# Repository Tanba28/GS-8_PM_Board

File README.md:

# GS-8_PM_Board
GS-8 Power Management Board

Master project -> [project-arrows/GS-8](https://github.com/project-arrows/GS-8)

## Overview
 * GS-8電源管理基板

## Role
 * 外部電源と内部電源の切り替えを行う。
 * 内部電源の電流・電圧を監視する。
 * 内部電源の電圧が規定値を下回った際にカットオフを行う。
 * CANバスを監視しロギングする。

## Link
 * [Tanba28/GS-8_PD_Board](https://github.com/Tanba28/GS-8_PD_Board)
 * [Tanba28/GS-8_Barometer](https://github.com/Tanba28/GS-8_Barometer)
 * [Tanba28/GS-8_Motion_Logger](https://github.com/Tanba28/GS-8_Motion_Logger)
 * [Tanba28/GS-8_Relay_Board](https://github.com/Tanba28/GS-8_Relay_Board)
 * [ringo156/GS-8_ACCLRM_Board](https://github.com/ringo156/GS-8_ACCLRM_Board)
 * [takamasavvv/RCT-X_Logger](https://github.com/takamasavvv/RCT-X-Logger)
 * [takamasavvv/RCT-X-Telemetry](https://github.com/takamasavvv/RCT-X-Telemetry)
 
## LICENSE
MIT License

Copyright (c) 2019 Tanba28

Permission is hereby granted, free of charge, to any person obtaining a copy
of this software and associated documentation files (the "Software"), to deal
in the Software without restriction, including without limitation the rights
to use, copy, modify, merge, publish, distribute, sublicense, and/or sell
copies of the Software, and to permit persons to whom the Software is
furnished to do so, subject to the following conditions:

The above copyright notice and this permission notice shall be included in all
copies or substantial portions of the Software.

THE SOFTWARE IS PROVIDED "AS IS", WITHOUT WARRANTY OF ANY KIND, EXPRESS OR
IMPLIED, INCLUDING BUT NOT LIMITED TO THE WARRANTIES OF MERCHANTABILITY,
FITNESS FOR A PARTICULAR PURPOSE AND NONINFRINGEMENT. IN NO EVENT SHALL THE
AUTHORS OR COPYRIGHT HOLDERS BE LIABLE FOR ANY CLAIM, DAMAGES OR OTHER
LIABILITY, WHETHER IN AN ACTION OF CONTRACT, TORT OR OTHERWISE, ARISING FROM,
OUT OF OR IN CONNECTION WITH THE SOFTWARE OR THE USE OR OTHER DEALINGS IN THE
SOFTWARE.

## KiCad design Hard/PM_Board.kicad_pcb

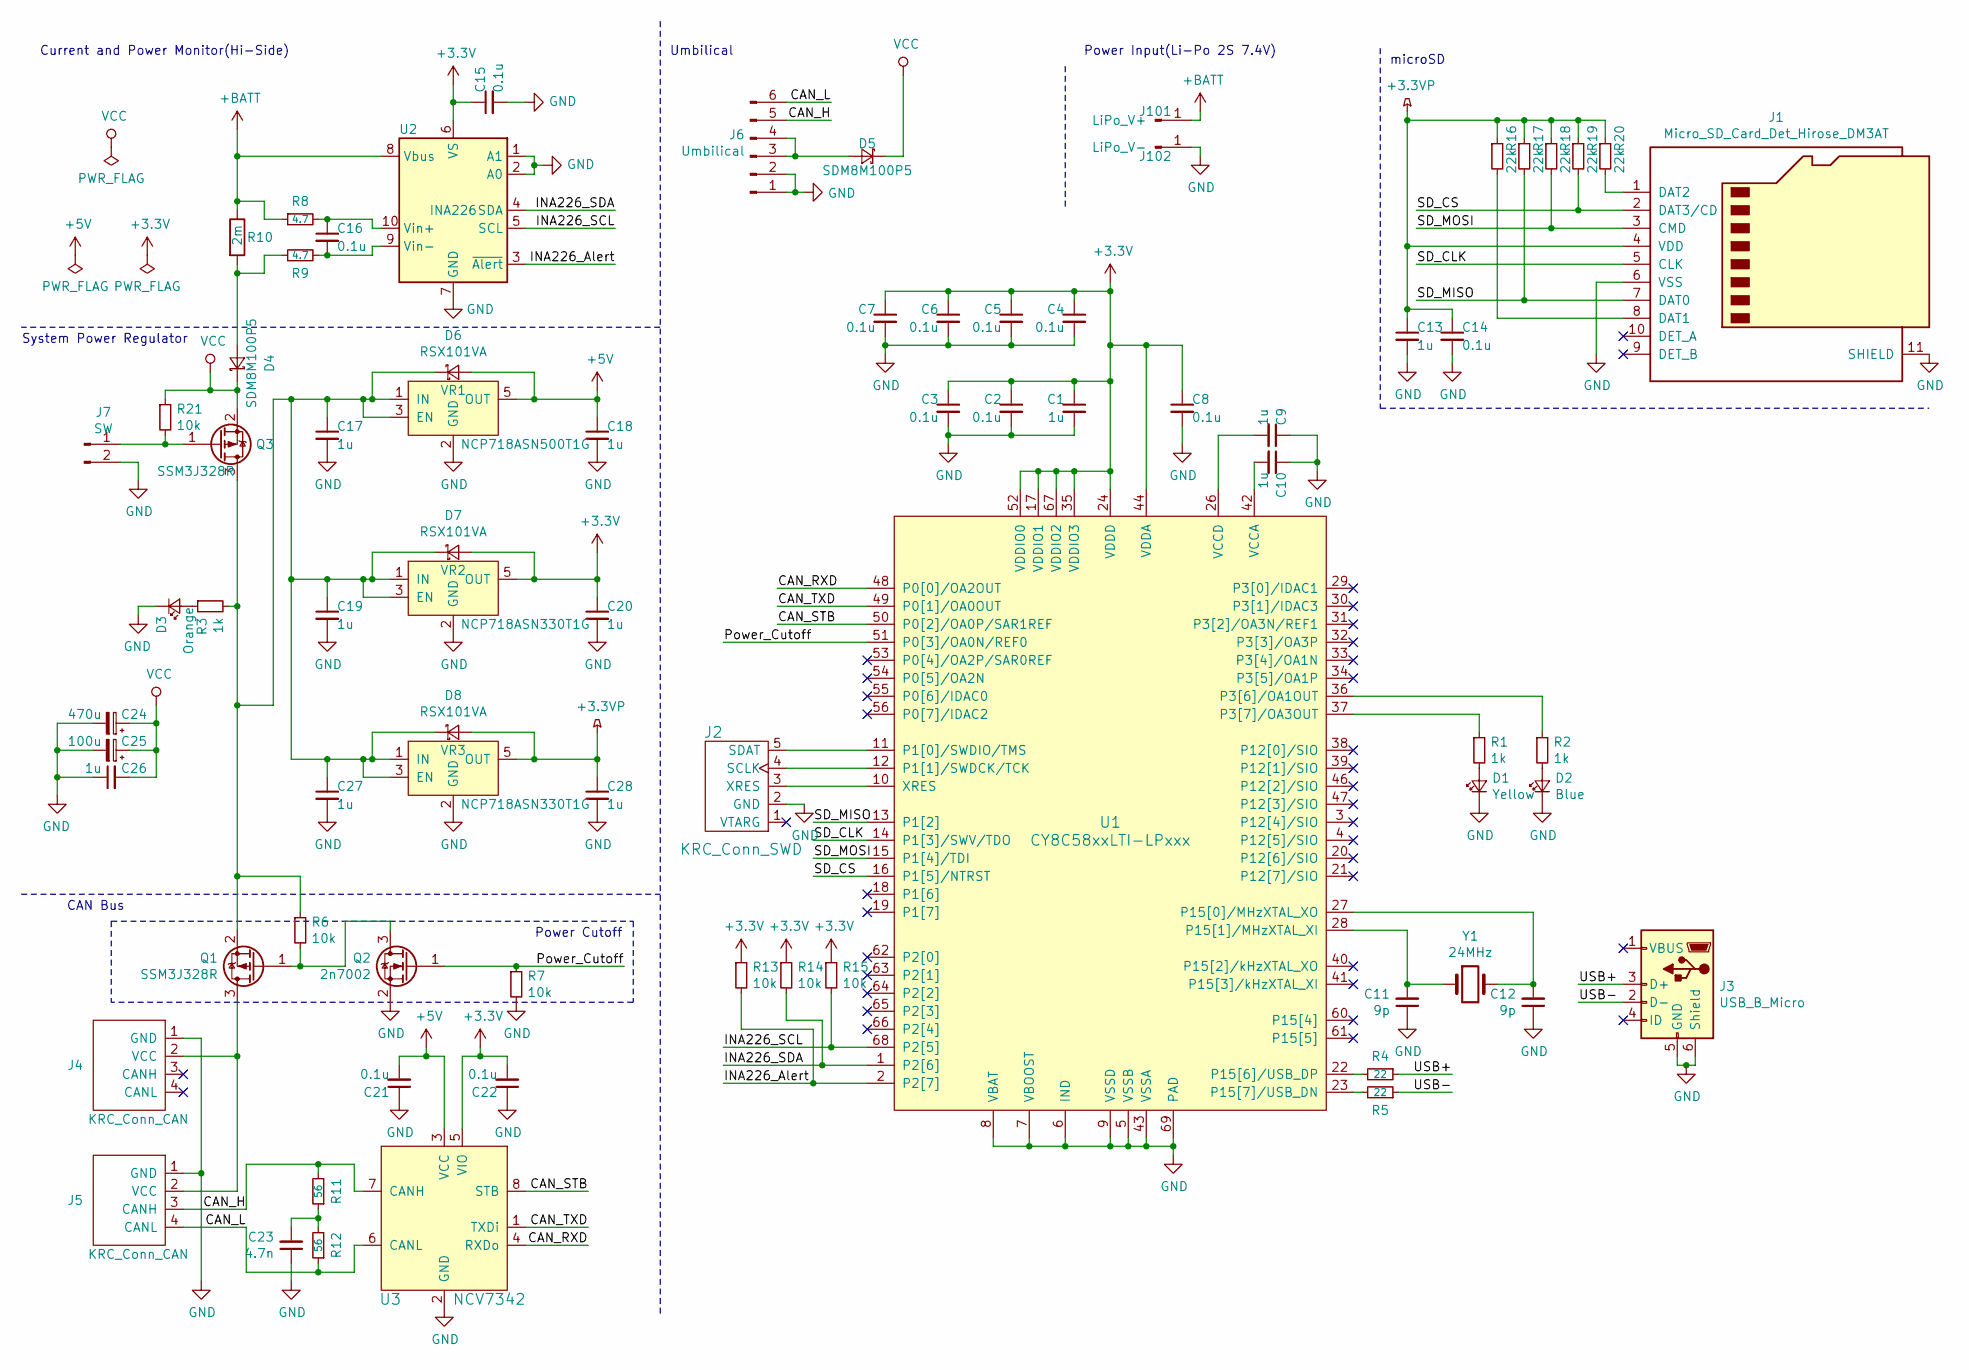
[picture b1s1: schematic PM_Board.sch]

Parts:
C1, C9, C10, C13, C17, C18, C19, C20, C26, C27, C28: 1u; C_0402_1005Metric; MPN GRM155R61E105KA12D
C2, C3, C4, C5, C6, C7, C8, C14, C15, C16, C21, C22: 0.1u; C_0402_1005Metric; MPN GRM155R62A104KE14D
C11, C12: 9p; C_0402_1005Metric; MPN GRM1555C1H9R0DA01D
C23: 4.7n; C_0402_1005Metric; MPN GRM155R71H472KA01D
C24: 470u; CP_Elec_10x10; MPN UWT1E471MNL1GS
C25: 100u; CP_Elec_6.3x7.7; MPN UWT1E101MCL1GS
D1: Yellow; LED_0603_1608Metric
D2: Blue; LED_0603_1608Metric
D3: Orange; LED_0603_1608Metric
D4, D5: SDM8M100P5; D_PowerDI5; MPN SDM8M100P5-13
D6, D7, D8: RSX101VA; D_TUMD2; MPN RSX101VAM-30TR
J1: Micro_SD_Card_Det_Hirose_DM3AT; microSD_HC_Hirose_DM3AT-SF-PEJM5; MPN DM3AT-SF-PEJM5
J2: KRC_Conn_SWD; JST_JQ_05JQ-BT_1x05_P2.5mm_Vertical; MPN 05JQ-BT
J3: USB_B_Micro; Hirose_ZX_ZX62D-B-5P8; MPN ZX62D-B-5P8(30)
J4, J5: KRC_Conn_CAN; JST_XH_S4B-XH-A_1x04_P2.50mm_Horizontal; MPN S4B-XH-A
J6: Umbilical; Hirose_DF1E_DF1E-6P-2.5DS_1x06_P2.5mm_Vertical; MPN DF1EC-6P-2.5DSA(35)
J7: SW; Hirose_DF1E_DF1E-2P-2.5DS_1x02_P2.5mm_Vertical; MPN DF1EC-2P-2.5DSA(35)
J101: LiPo_V+; MountingHole_2.2mm_M2_Pad_Via
J102: LiPo_V-; MountingHole_2.2mm_M2_Pad_Via
Q1, Q3: SSM3J328R; SOT-23; MPN SSM3J328R,LF
Q2: 2n7002; SOT-23; MPN 2N7002
R1, R2, R3: 1k; R_0402_1005Metric; MPN ERJ-2GEJ102X
R4, R5: 22; R_0402_1005Metric; MPN ERJ-2GEJ220X
R6, R7, R13, R14, R15, R21: 10k; R_0402_1005Metric; MPN ERJ-2GEJ103X
R8, R9: 4.7; R_0402_1005Metric; MPN ERJ-2GEJ4R7X
R10: 2m; R_0805_2012Metric; MPN PMR10EZPFV2L00
R11, R12: 56; R_0402_1005Metric; MPN ERJ-2GEJ560X
R16, R17, R18, R19, R20: 22k; R_0402_1005Metric; MPN ERJ-2RKF2202X
U1: CY8C58xxLTI-LPxxx; Cypress_QFN-68_EP_8x8_Pitch0.4mm; MPN CY8C5868LTI-LP039
U2: INA226; MSOP-10_3x3mm_P0.5mm; MPN INA226AIDGSR
U3: NCV7342; DFN-8-1EP_3x3mm_P0.65mm_EP1.55x2.4mm; MPN NCV7342MW3R2G
VR1: NCP718ASN500T1G; TSOT-23-5; MPN NCP718ASN500T1G
VR2, VR3: NCP718ASN330T1G; TSOT-23-5; MPN NCP718ASN330T1G
Y1: 24MHz; Crystal_Murata_XRCHA; MPN XRCHA24M000F0A01R0

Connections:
+3.3VP: C13.1, C14.1, C28.1, D8.2 (A), J1.4 (VDD), R16.1, R17.1, R18.1, R19.1, R20.1, VR3.5 (OUT)
+3V3: C1.1, C2.1, C3.1, C4.1, C5.1, C6.1, C7.1, C8.1, C15.1, C20.1, C22.2, D7.2 (A), R13.1, R14.1, R15.1, U1.17 (VDDIO1), U1.24 (VDDD), U1.35 (VDDIO3), U1.44 (VDDA), U1.52 (VDDIO0), U1.59 (VDDD), U1.67 (VDDIO2), U2.6 (VS), U3.5 (VIO), VR2.5 (OUT)
+5V: C18.1, C21.2, D6.2 (A), U3.3 (VCC), VR1.5 (OUT)
+BATT: J101.1, R8.1, R10.1, U2.8 (Vbus)
/CAN_H: J5.3 (CANH), J6.5, R11.2, U3.7 (CANH)
/CAN_L: J5.4 (CANL), J6.6, R12.1, U3.6 (CANL)
/CAN_RXD: U1.48 (P0[0]/OA2OUT), U3.4 (RXDo)
/CAN_STB: U1.50 (P0[2]/OA0P/SAR1REF), U3.8 (STB)
/CAN_TXD: U1.49 (P0[1]/OA0OUT), U3.1 (TXDi)
/INA226_Alert: R13.2, U1.2 (P2[7]), U2.3 (~Alert~)
/INA226_SCL: R15.2, U1.68 (P2[5]), U2.5 (SCL)
/INA226_SDA: R14.2, U1.1 (P2[6]), U2.4 (SDA)
/Power_Cutoff: Q2.1 (G), R7.1, U1.51 (P0[3]/OA0N/REF0)
/SD_CLK: J1.5 (CLK), U1.14 (P1[3]/SWV/TDO)
/SD_CS: J1.2 (DAT3/CD), R19.2, U1.16 (P1[5]/NTRST)
/SD_MISO: J1.7 (DAT0), R17.2, U1.13 (P1[2])
/SD_MOSI: J1.3 (CMD), R18.2, U1.15 (P1[4]/TDI)
/USB+: J3.3 (D+), R4.1
/USB-: J3.2 (D-), R5.1
GND: C1.2, C2.2, C3.2, C4.2, C5.2, C6.2, C7.2, C8.2, C9.1, C10.1, C11.1, C12.1, C13.2, C14.2, C15.2, C17.2, C18.2, C19.2, C20.2, C21.1, C22.1, C23.1, C24.2, C25.2, C26.1, C27.2, C28.2, D1.1 (K), D2.1 (K), D3.1 (K), J1.6 (VSS), J1.11 (SHIELD), J2.2 (GND), J3.5 (GND), J3.6 (Shield), J4.1 (GND), J5.1 (GND), J6.1, J6.2, J7.2, J102.1, Q2.2 (S), R7.2, U1.5 (VSSB), U1.6 (IND), U1.7 (VBOOST), U1.8 (VBAT), U1.9 (VSSD), U1.25 (VSSD), U1.43 (VSSA), U1.45 (VSSD), U1.58 (VSSD), U1.69 (PAD), U2.1 (A1), U2.2 (A0), U2.7 (GND), U3.2 (GND), U3.9, VR1.2 (GND), VR2.2 (GND), VR3.2 (GND)
unnamed: C9.2, U1.26 (VCCD), U1.57 (VCCD)
unnamed: C10.2, U1.42 (VCCA)
unnamed: C11.2, U1.28 (P15[1]/MHzXTAL_XI), Y1.1
unnamed: C12.2, U1.27 (P15[0]/MHzXTAL_XO), Y1.2
unnamed: C16.1, R8.2, U2.10 (Vin+)
unnamed: C16.2, R9.2, U2.9 (Vin-)
unnamed: C17.1, C19.1, C27.1, D6.1 (K), D7.1 (K), D8.1 (K), Q1.2 (S), Q3.3 (D), R3.2, R6.1, VR1.1 (IN), VR1.3 (EN), VR2.1 (IN), VR2.3 (EN), VR3.1 (IN), VR3.3 (EN)
unnamed: C23.2, R11.1, R12.2
unnamed: D1.2 (A), R1.2
unnamed: D2.2 (A), R2.2
unnamed: D3.2 (A), R3.1
unnamed: D4.2 (A), R9.1, R10.2
unnamed: D5.2 (A), J6.3, J6.4
unnamed: J1.1 (DAT2), R20.2
unnamed: J1.8 (DAT1), R16.2
unnamed: J2.3 (XRES), U1.10 (XRES)
unnamed: J2.4 (SCLK), U1.12 (P1[1]/SWDCK/TCK)
unnamed: J2.5 (SDAT), U1.11 (P1[0]/SWDIO/TMS)
unnamed: J4.2 (VCC), J5.2 (VCC), Q1.3 (D)
unnamed: J7.1, Q3.1 (G), R21.2
unnamed: Q1.1 (G), Q2.3 (D), R6.2
unnamed: R1.1, U1.37 (P3[7]/OA3OUT)
unnamed: R2.1, U1.36 (P3[6]/OA1OUT)
unnamed: R4.2, U1.22 (P15[6]/USB_DP)
unnamed: R5.2, U1.23 (P15[7]/USB_DN)
VCC: C24.1, C25.1, C26.2, D4.1 (K), D5.1 (K), Q3.2 (S), R21.1

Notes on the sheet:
Power Input(Li-Po 2S 7.4V)
Current and Power Monitor(Hi-Side)
System Power Regulator
CAN Bus
Power Cutoff
Umbilical
microSD

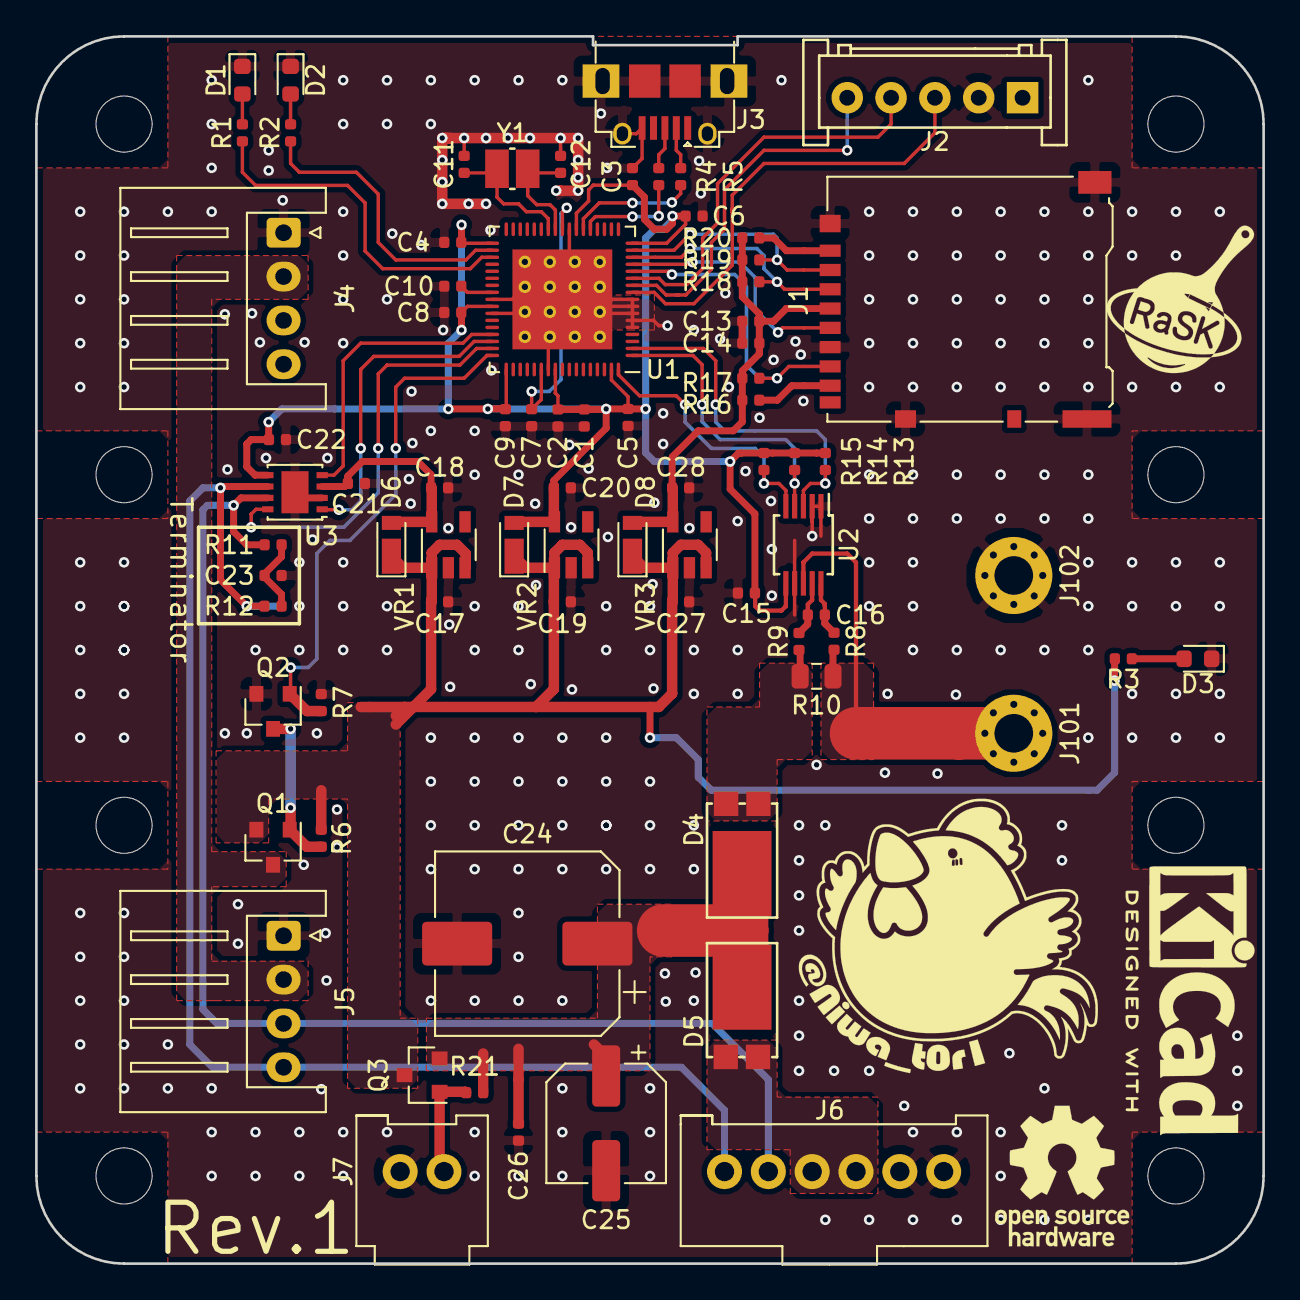
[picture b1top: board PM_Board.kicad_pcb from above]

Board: 2 copper layers, 70.0 x 70.0 mm, 76 parts (0 on the bottom side), 46 nets.

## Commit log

2019-09-20 [add] プロジェクトファイル作成
2019-09-20 [add] マイコン・SD・電源周りを配置
2019-09-21 [add] フットプリントの割当を完了
2019-09-21 [add] PCBの基板外形を作った
2019-09-24 [add] 電源系のダイオードをアンビリカル側にも追加
2019-09-24 [add] 部品配置仮完了
2019-09-24 [update] ライブラリのライセンス表記更新
2019-09-24 [update] カットオフ用のFETをPchに変更してハイサイドへ移動
2019-09-24 [update] ミスを修正
2019-09-24 [add] 配線中だよ
2019-09-25 [add] 基板完成
2019-09-25 [add] pdf、SVGを追加
2019-09-29 [add] 逆流防止用ダイオードを追加
2019-10-02 [update] パターンを編集完了
2019-10-02 [update] アンビリカルをDF1Eに変更
2019-10-02 [update] 部品の干渉を修正
2019-10-04 [update] SDカード用のLDOを追加
2019-10-09 [add] ダイオードの選定を変更。PchMOSFETの選定を変更。パターンを引き直し。ガーバ出力
2019-10-09 [update] パスコンの位置を変更
2019-10-12 [add] USBに切り欠きを追加.ガーバー出力
2019-10-12 [update] READMEを整備
